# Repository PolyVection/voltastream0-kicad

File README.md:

# VoltaStream ZERO hardware 

PolyVection VoltaStream ZERO is an open source audio streaming solution that runs Linux and features a high quality digital-to-analog converter as well as digital TOSLINK output capability. There is also a 40 way pinheader with access to 28 GPIO's. It is as small as 65 mm x 30 mm and very efficient. This PCB was created using KiCAD 4.0.5.
The whole project is released under the Creative Commons BY-NC-ND 3.0 license. 
For details please refere to the full license text at https://creativecommons.org/licenses/by-nc-nd/3.0/legalcode

If you have any questions don't hesitate to contact us. We are also offering customisation and prototyping services. http://www.voltastream.com

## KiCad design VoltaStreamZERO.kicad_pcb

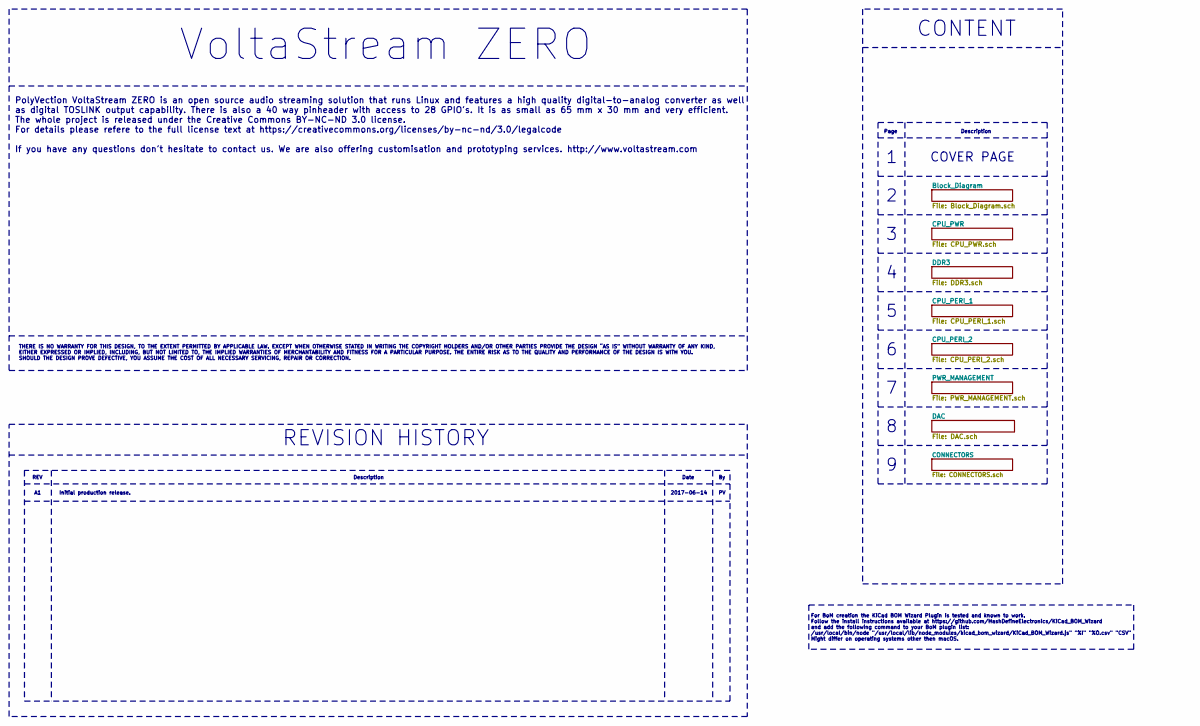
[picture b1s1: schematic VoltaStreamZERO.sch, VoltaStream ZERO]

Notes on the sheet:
VoltaStream ZERO
REVISION HISTORY
CONTENT
THERE IS NO WARRANTY FOR THIS DESIGN, TO THE EXTENT PERMITTED BY APPLICABLE LAW. EXCEPT WHEN OTHERWISE STATED IN WRITING THE COPYRIGHT HOLDERS AND/OR OTHER PARTIES PROVIDE THE DESIGN “AS IS” WITHOUT WARRANTY OF ANY KIND, EITHER EXPRESSED OR IMPLIED, INCLUDING, BUT NOT LIMITED TO, THE IMPLIED WARRAN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
PolyVection VoltaStream ZERO is an open source audio streaming solution that runs Linux and features a high quality digital-to-analog converter as well as digital TOSLINK output capability. There is also a 40 way pinheader with access to 28 GPIO's. It is as small as 65 mm x 30 mm and very efficient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
Page
Description
COVER PAGE
For BoM creation the KiCad BOM Wizard Plugin is tested and known to work. Follow the install instructions available at https://github.com/HashDefineElectronics/KiCad_BOM_Wizard and add the following command to your BoM plugin list: /usr/local/bin/node "/usr/local/lib/node_modules/kicad_bom_wizard/K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
REV
Date
Initial production release.
2017-06-14

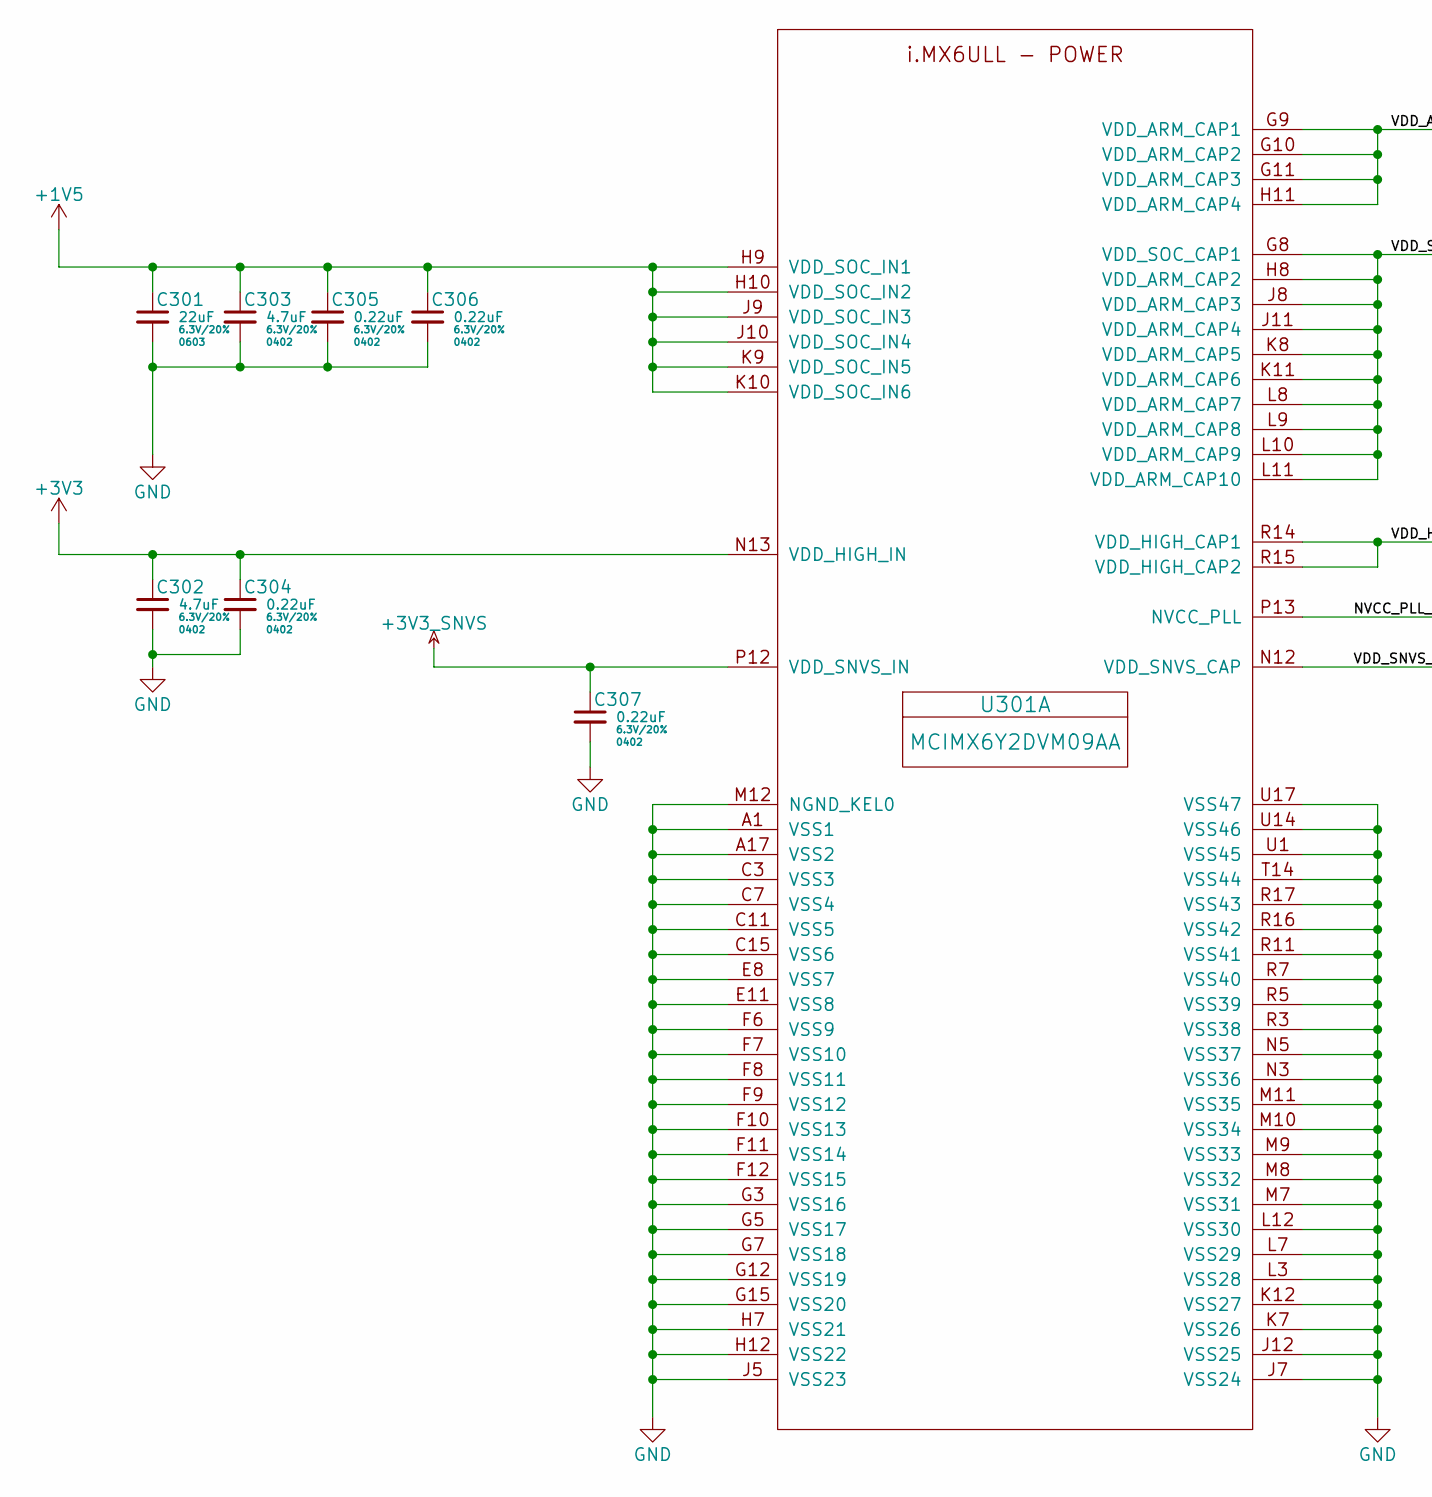
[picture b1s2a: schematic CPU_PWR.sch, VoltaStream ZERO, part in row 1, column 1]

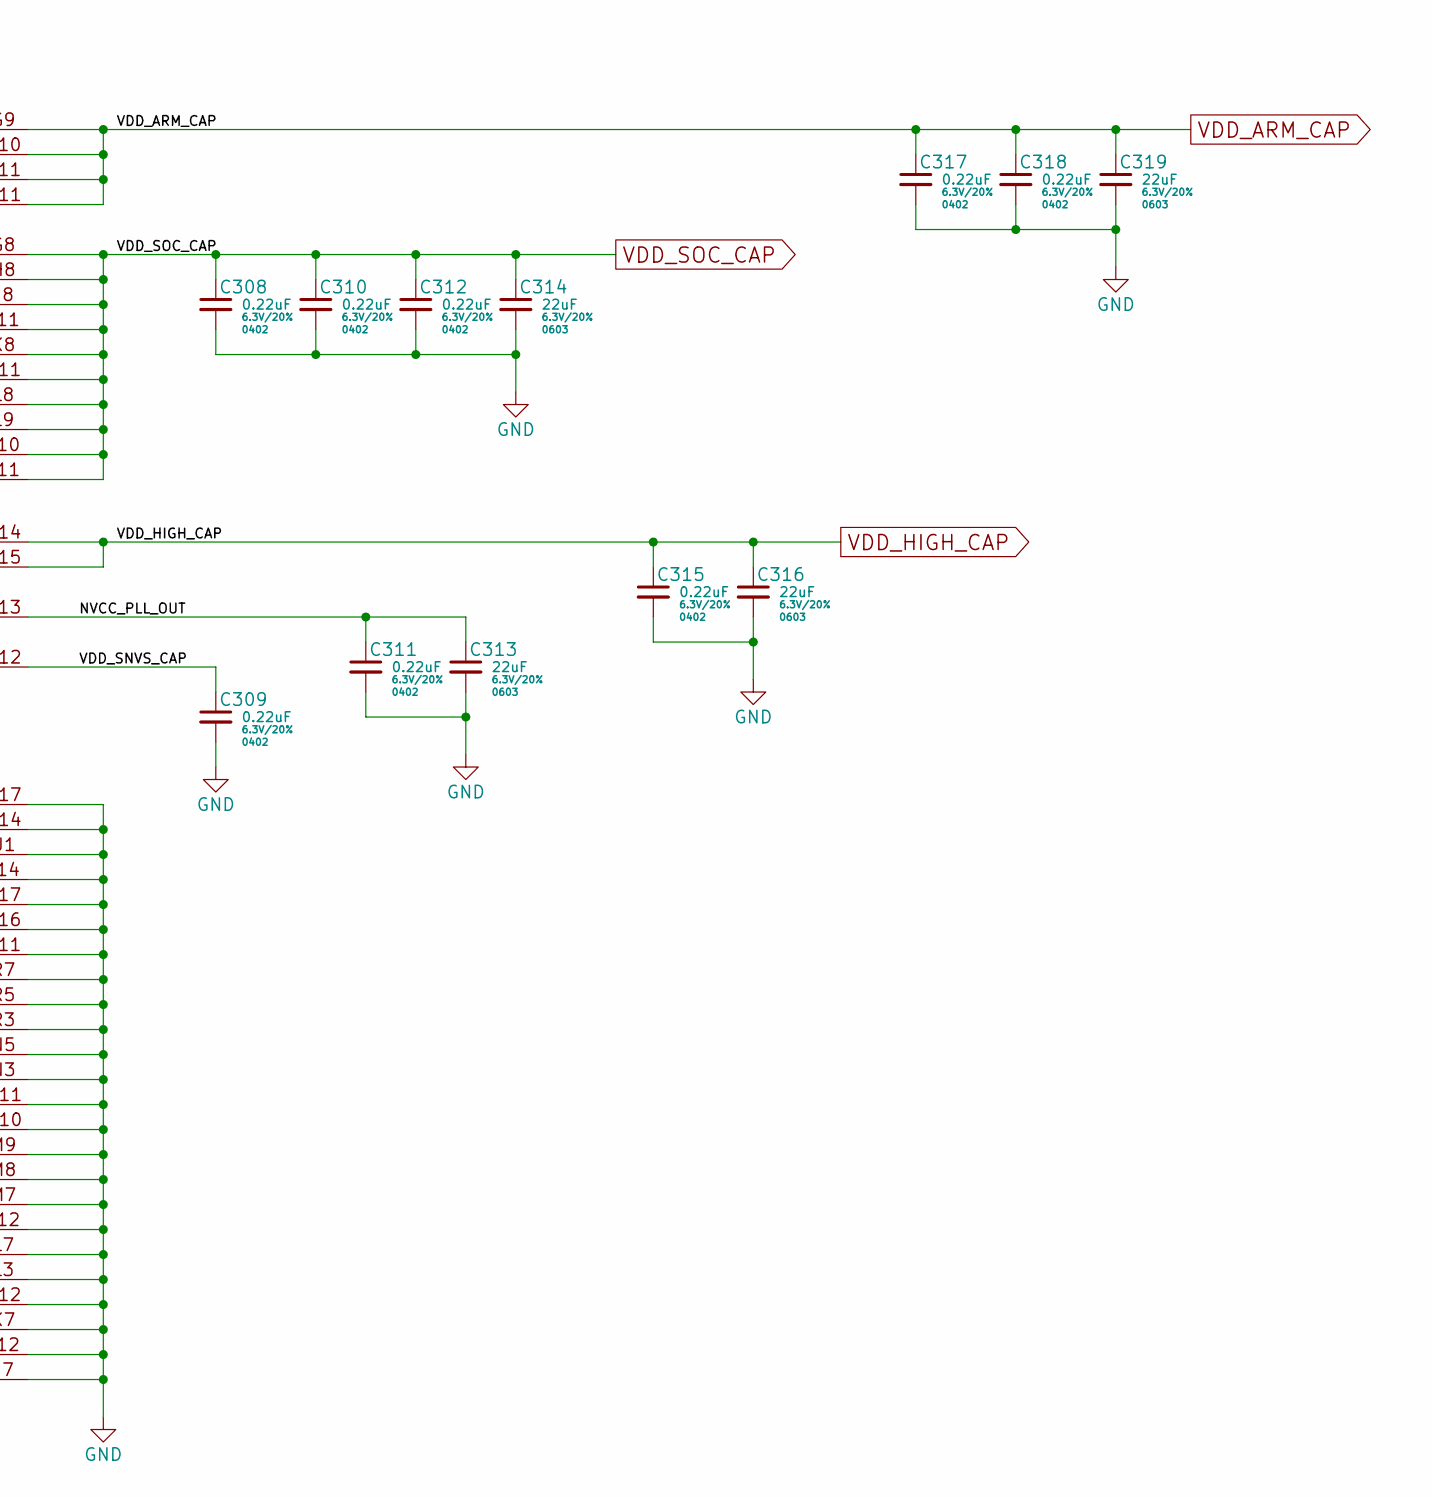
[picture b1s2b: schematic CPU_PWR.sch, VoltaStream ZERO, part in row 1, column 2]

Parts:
C301, C313, C314, C316, C319: 22uF; 0603; Rating 6.3V/20%; Rating2 X5R; Part GRM188R60J226ME0D
C302, C303: 4.7uF; 0402; Rating 6.3V/20%; Rating2 X5R; Part GRM155R60J475ME7D
C304, C305, C306, C307, C308, C309, C310, C311, C312, C315, C317, C318: 0.22uF; 0402; Rating 6.3V/20%; Rating2 X5R; Part GRM155R60J224KE01D
U301: MCIMX6Y2DVM09AA; BGA_14x14; Rating 1x 900 MHz, 32 bit; Part MCIMX6Y2DVM09AA

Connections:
+1V5: C301.1, C303.1, C305.1, C306.1, U301.H9 (VDD_SOC_IN1), U301.H10 (VDD_SOC_IN2), U301.J9 (VDD_SOC_IN3), U301.J10 (VDD_SOC_IN4), U301.K9 (VDD_SOC_IN5), U301.K10 (VDD_SOC_IN6); also elsewhere on the board
+3V3: C302.1, C304.1, U301.N13 (VDD_HIGH_IN); also elsewhere on the board
+3V3_SNVS: C307.1, U301.P12 (VDD_SNVS_IN); also elsewhere on the board
/CPU_PWR/NVCC_PLL_OUT: C311.1, C313.1, U301.P13 (NVCC_PLL)
/CPU_PWR/VDD_SNVS_CAP: C309.1, U301.N12 (VDD_SNVS_CAP)
GND: C301.2, C302.2, C303.2, C304.2, C305.2, C306.2, C307.2, C308.2, C309.2, C310.2, C311.2, C312.2, C313.2, C314.2, C315.2, C316.2, C317.2, C318.2, C319.2, U301.A1 (VSS1), U301.A17 (VSS2), U301.C3 (VSS3), U301.C7 (VSS4), U301.C11 (VSS5), U301.C15 (VSS6), U301.E8 (VSS7), U301.E11 (VSS8), U301.F6 (VSS9), U301.F7 (VSS10), U301.F8 (VSS11), U301.F9 (VSS12), U301.F10 (VSS13), U301.F11 (VSS14), U301.F12 (VSS15), U301.G3 (VSS16), U301.G5 (VSS17), U301.G7 (VSS18), U301.G12 (VSS19), U301.G15 (VSS20), U301.H7 (VSS21), U301.H12 (VSS22), U301.J5 (VSS23), U301.J7 (VSS24), U301.J12 (VSS25), U301.K7 (VSS26), U301.K12 (VSS27), U301.L3 (VSS28), U301.L7 (VSS29), U301.L12 (VSS30), U301.M7 (VSS31), U301.M8 (VSS32), U301.M9 (VSS33), U301.M10 (VSS34), U301.M11 (VSS35), U301.M12 (NGND_KEL0), U301.N3 (VSS36), U301.N5 (VSS37), U301.R3 (VSS38), U301.R5 (VSS39), U301.R7 (VSS40), U301.R11 (VSS41), U301.R16 (VSS42), U301.R17 (VSS43), U301.T14 (VSS44), U301.U1 (VSS45), U301.U14 (VSS46), U301.U17 (VSS47); also elsewhere on the board
VDD_ARM_CAP: C317.1, C318.1, C319.1, U301.G9 (VDD_ARM_CAP1), U301.G10 (VDD_ARM_CAP2), U301.G11 (VDD_ARM_CAP3), U301.H11 (VDD_ARM_CAP4)
VDD_HIGH_CAP: C315.1, C316.1, U301.R14 (VDD_HIGH_CAP1), U301.R15 (VDD_HIGH_CAP2); also elsewhere on the board
VDD_SOC_CAP: C308.1, C310.1, C312.1, C314.1, U301.G8 (VDD_SOC_CAP1), U301.H8 (VDD_ARM_CAP2), U301.J8 (VDD_ARM_CAP3), U301.J11 (VDD_ARM_CAP4), U301.K8 (VDD_ARM_CAP5), U301.K11 (VDD_ARM_CAP6), U301.L8 (VDD_ARM_CAP7), U301.L9 (VDD_ARM_CAP8), U301.L10 (VDD_ARM_CAP9), U301.L11 (VDD_ARM_CAP10)

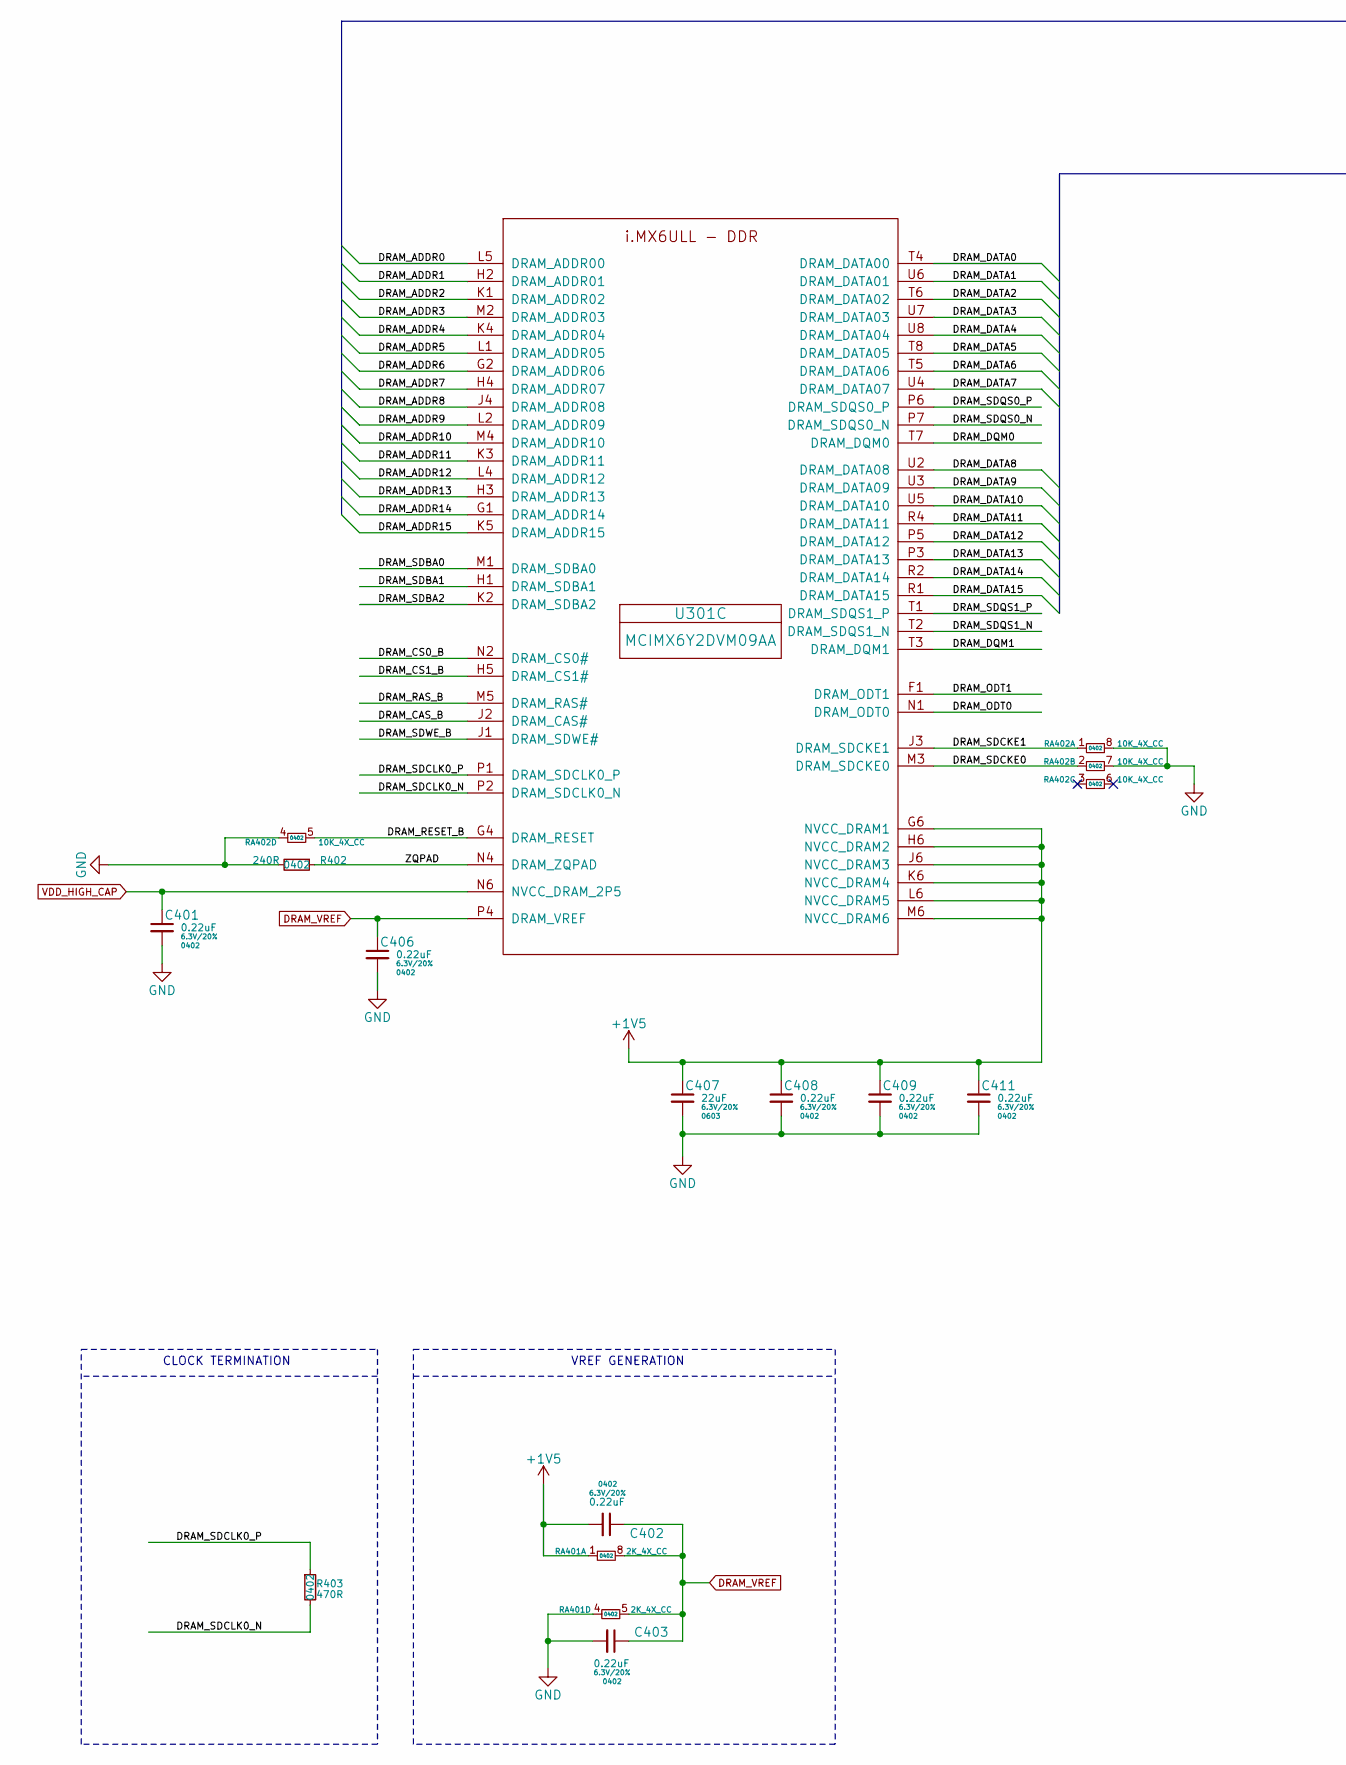
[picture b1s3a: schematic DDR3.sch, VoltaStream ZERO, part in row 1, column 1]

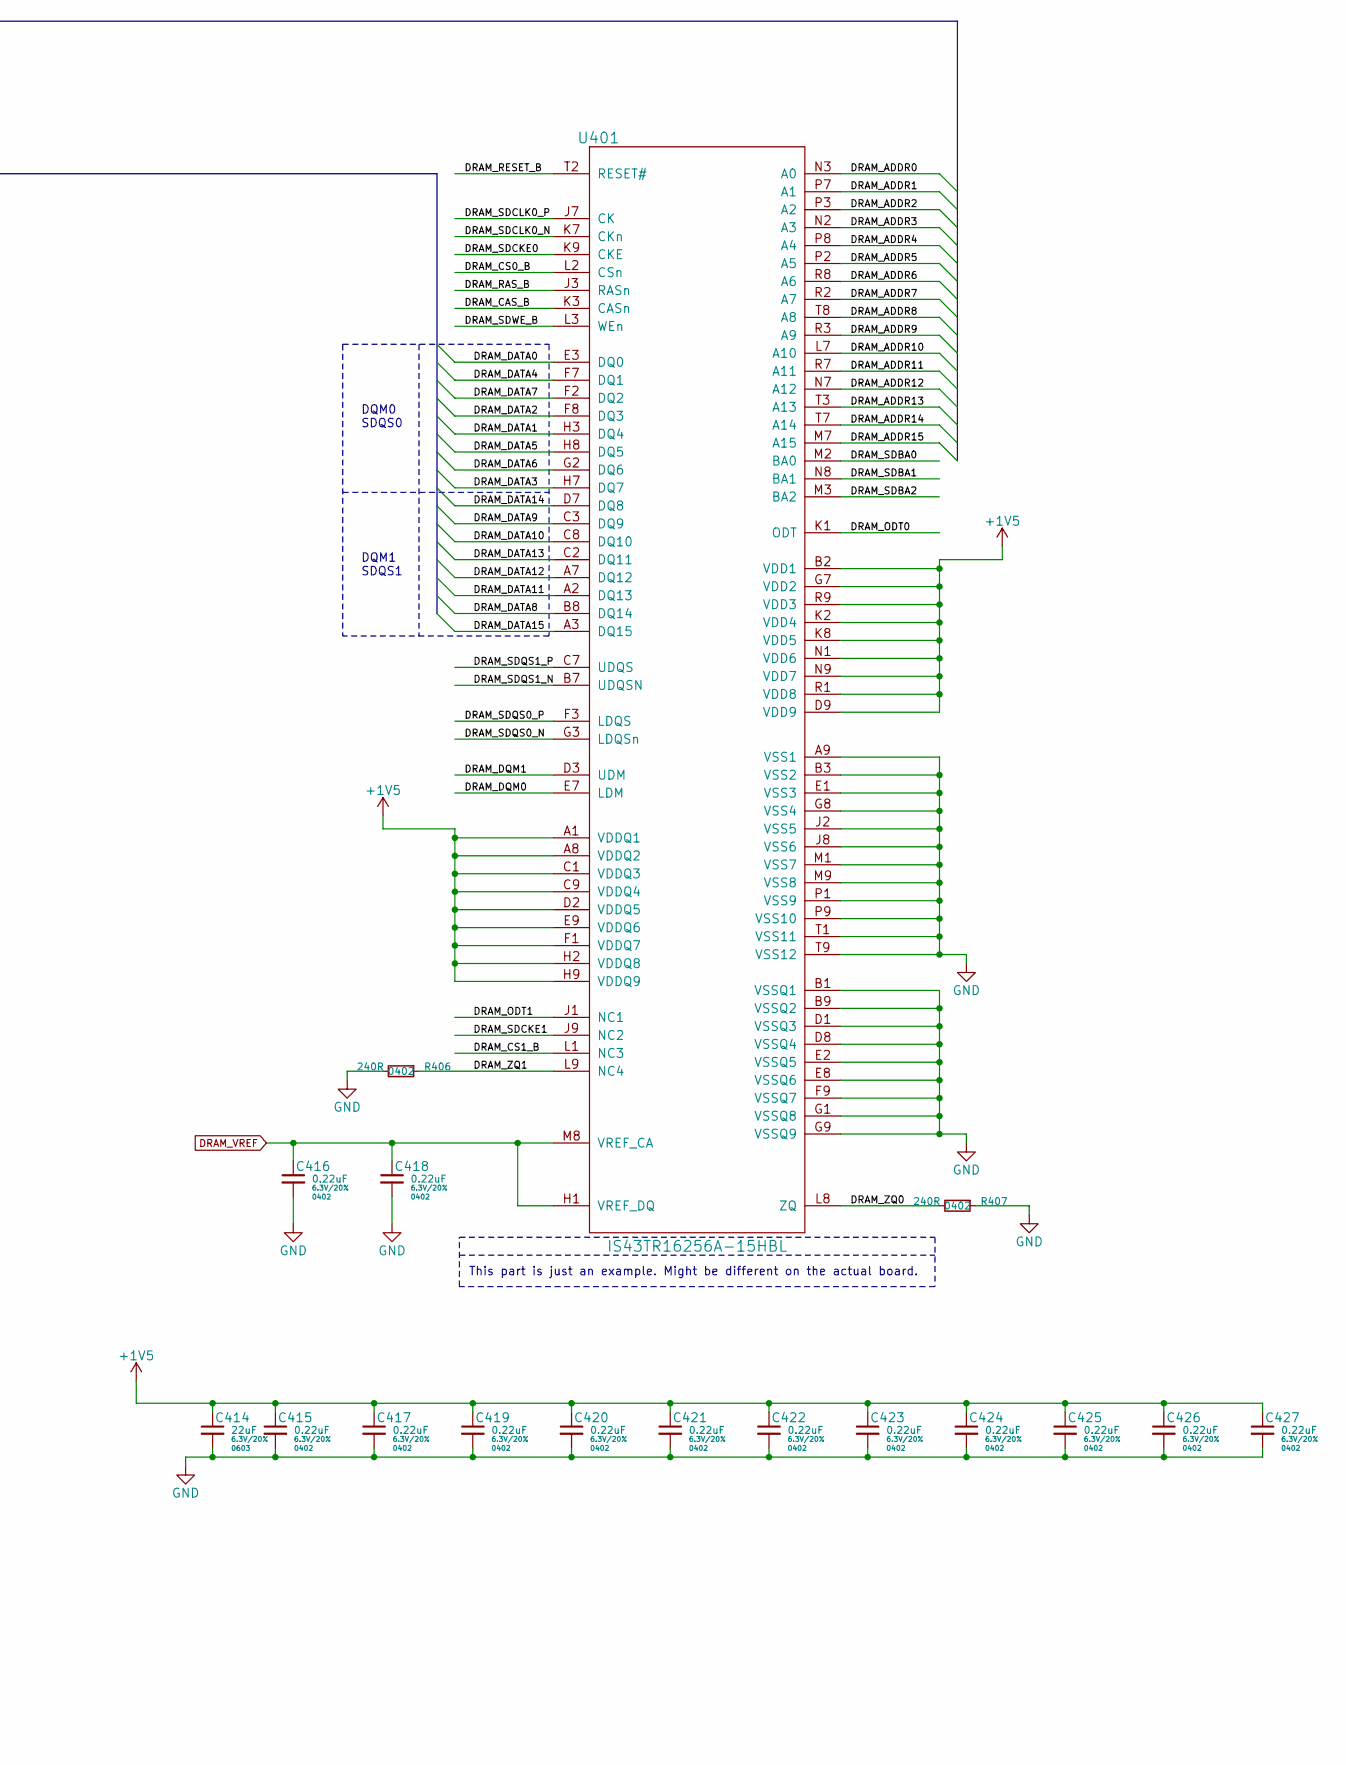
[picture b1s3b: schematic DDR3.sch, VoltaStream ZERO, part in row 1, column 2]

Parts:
C401, C402, C403, C406, C408, C409, C411, C415, C416, C417, C418, C419, C420, C421, C422, C423, C424, C425, C426, C427: 0.22uF; 0402; Rating 6.3V/20%; Rating2 X5R; Part GRM155R60J224KE01D
C407, C414: 22uF; 0603; Rating 6.3V/20%; Rating2 X5R; Part GRM188R60J226ME0D
R402, R406, R407: 240R; 0402; Rating 1% / Thick Film; Part RC0402FR-07240RL
R403: 470R; 0402; Rating 1% / Thick Film; Part RC0402FR-07470RL
RA401: 2K_4X_CC; R_Array_OPT_4x0402; Rating 2K, 5%; Rating2 Concave Array 4x; Part EXB-N8V202JX
RA402: 10K_4X_CC; R_Array_OPT_4x0402; Rating 10K, 5%; Rating2 Concave Array 4x; Part EXB-N8V103JX
U301: MCIMX6Y2DVM09AA; BGA_14x14; Rating 1x 900 MHz, 32 bit; Part MCIMX6Y2DVM09AA
U401: IS43TR16256A-15HBL; FBGA_96_DDR3L; Rating 4G - DDR3; Rating2 512 MB - 1V5; Part IS43TR16256A-15HBL

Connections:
+1V5: C402.2, C407.1, C408.1, C409.1, C411.1, C414.1, C415.1, C417.1, C419.1, C420.1, C421.1, C422.1, C423.1, C424.1, C425.1, C426.1, C427.1, RA401.1, U301.G6 (NVCC_DRAM1), U301.H6 (NVCC_DRAM2), U301.J6 (NVCC_DRAM3), U301.K6 (NVCC_DRAM4), U301.L6 (NVCC_DRAM5), U301.M6 (NVCC_DRAM6), U401.A1 (VDDQ1), U401.A8 (VDDQ2), U401.B2 (VDD1), U401.C1 (VDDQ3), U401.C9 (VDDQ4), U401.D2 (VDDQ5), U401.D9 (VDD9), U401.E9 (VDDQ6), U401.F1 (VDDQ7), U401.G7 (VDD2), U401.H2 (VDDQ8), U401.H9 (VDDQ9), U401.K2 (VDD4), U401.K8 (VDD5), U401.N1 (VDD6), U401.N9 (VDD7), U401.R1 (VDD8), U401.R9 (VDD3); also elsewhere on the board
/DDR3/DRAM_ADDR0: U301.L5 (DRAM_ADDR00), U401.N3 (A0)
/DDR3/DRAM_ADDR1: U301.H2 (DRAM_ADDR01), U401.P7 (A1)
/DDR3/DRAM_ADDR2: U301.K1 (DRAM_ADDR02), U401.P3 (A2)
/DDR3/DRAM_ADDR3: U301.M2 (DRAM_ADDR03), U401.N2 (A3)
/DDR3/DRAM_ADDR4: U301.K4 (DRAM_ADDR04), U401.P8 (A4)
/DDR3/DRAM_ADDR5: U301.L1 (DRAM_ADDR05), U401.P2 (A5)
/DDR3/DRAM_ADDR6: U301.G2 (DRAM_ADDR06), U401.R8 (A6)
/DDR3/DRAM_ADDR7: U301.H4 (DRAM_ADDR07), U401.R2 (A7)
/DDR3/DRAM_ADDR8: U301.J4 (DRAM_ADDR08), U401.T8 (A8)
/DDR3/DRAM_ADDR9: U301.L2 (DRAM_ADDR09), U401.R3 (A9)
/DDR3/DRAM_ADDR10: U301.M4 (DRAM_ADDR10), U401.L7 (A10)
/DDR3/DRAM_ADDR11: U301.K3 (DRAM_ADDR11), U401.R7 (A11)
/DDR3/DRAM_ADDR12: U301.L4 (DRAM_ADDR12), U401.N7 (A12)
/DDR3/DRAM_ADDR13: U301.H3 (DRAM_ADDR13), U401.T3 (A13)
/DDR3/DRAM_ADDR14: U301.G1 (DRAM_ADDR14), U401.T7 (A14)
/DDR3/DRAM_ADDR15: U301.K5 (DRAM_ADDR15), U401.M7 (A15)
/DDR3/DRAM_CAS_B: U301.J2 (DRAM_CAS#), U401.K3 (CASn)
/DDR3/DRAM_CS0_B: U301.N2 (DRAM_CS0#), U401.L2 (CSn)
/DDR3/DRAM_CS1_B: U301.H5 (DRAM_CS1#), U401.L1 (NC3)
/DDR3/DRAM_DATA0: U301.T4 (DRAM_DATA00), U401.E3 (DQ0)
/DDR3/DRAM_DATA1: U301.U6 (DRAM_DATA01), U401.H3 (DQ4)
/DDR3/DRAM_DATA2: U301.T6 (DRAM_DATA02), U401.F8 (DQ3)
/DDR3/DRAM_DATA3: U301.U7 (DRAM_DATA03), U401.H7 (DQ7)
/DDR3/DRAM_DATA4: U301.U8 (DRAM_DATA04), U401.F7 (DQ1)
/DDR3/DRAM_DATA5: U301.T8 (DRAM_DATA05), U401.H8 (DQ5)
/DDR3/DRAM_DATA6: U301.T5 (DRAM_DATA06), U401.G2 (DQ6)
/DDR3/DRAM_DATA7: U301.U4 (DRAM_DATA07), U401.F2 (DQ2)
/DDR3/DRAM_DATA8: U301.U2 (DRAM_DATA08), U401.B8 (DQ14)
/DDR3/DRAM_DATA9: U301.U3 (DRAM_DATA09), U401.C3 (DQ9)
/DDR3/DRAM_DATA10: U301.U5 (DRAM_DATA10), U401.C8 (DQ10)
/DDR3/DRAM_DATA11: U301.R4 (DRAM_DATA11), U401.A2 (DQ13)
/DDR3/DRAM_DATA12: U301.P5 (DRAM_DATA12), U401.A7 (DQ12)
/DDR3/DRAM_DATA13: U301.P3 (DRAM_DATA13), U401.C2 (DQ11)
/DDR3/DRAM_DATA14: U301.R2 (DRAM_DATA14), U401.D7 (DQ8)
/DDR3/DRAM_DATA15: U301.R1 (DRAM_DATA15), U401.A3 (DQ15)
/DDR3/DRAM_DQM0: U301.T7 (DRAM_DQM0), U401.E7 (LDM)
/DDR3/DRAM_DQM1: U301.T3 (DRAM_DQM1), U401.D3 (UDM)
/DDR3/DRAM_ODT0: U301.N1 (DRAM_ODT0), U401.K1 (ODT)
/DDR3/DRAM_ODT1: U301.F1 (DRAM_ODT1), U401.J1 (NC1)
/DDR3/DRAM_RAS_B: U301.M5 (DRAM_RAS#), U401.J3 (RASn)
/DDR3/DRAM_RESET_B: RA402.5 (R1), U301.G4 (DRAM_RESET), U401.T2 (RESET#)
/DDR3/DRAM_SDBA0: U301.M1 (DRAM_SDBA0), U401.M2 (BA0)
/DDR3/DRAM_SDBA1: U301.H1 (DRAM_SDBA1), U401.N8 (BA1)
/DDR3/DRAM_SDBA2: U301.K2 (DRAM_SDBA2), U401.M3 (BA2)
/DDR3/DRAM_SDCKE0: RA402.2 (P1), U301.M3 (DRAM_SDCKE0), U401.K9 (CKE)
/DDR3/DRAM_SDCKE1: RA402.1, U301.J3 (DRAM_SDCKE1), U401.J9 (NC2)
/DDR3/DRAM_SDCLK0_N: R403.2, U301.P2 (DRAM_SDCLK0_N), U401.K7 (CKn)
/DDR3/DRAM_SDCLK0_P: R403.1, U301.P1 (DRAM_SDCLK0_P), U401.J7 (CK)
/DDR3/DRAM_SDQS0_N: U301.P7 (DRAM_SDQS0_N), U401.G3 (LDQSn)
/DDR3/DRAM_SDQS0_P: U301.P6 (DRAM_SDQS0_P), U401.F3 (LDQS)
/DDR3/DRAM_SDQS1_N: U301.T2 (DRAM_SDQS1_N), U401.B7 (UDQSN)
/DDR3/DRAM_SDQS1_P: U301.T1 (DRAM_SDQS1_P), U401.C7 (UDQS)
/DDR3/DRAM_SDWE_B: U301.J1 (DRAM_SDWE#), U401.L3 (WEn)
/DDR3/DRAM_ZQ0: R407.2, U401.L8 (ZQ)
/DDR3/DRAM_ZQ1: R406.1, U401.L9 (NC4)
/DDR3/ZQPAD: R402.1, U301.N4 (DRAM_ZQPAD)
DRAM_VREF: C402.1, C403.1, C406.1, C416.1, C418.1, RA401.5 (R1), RA401.8 (R1), U301.P4 (DRAM_VREF), U401.H1 (VREF_DQ), U401.M8 (VREF_CA)
GND: C401.2, C403.2, C406.2, C407.2, C408.2, C409.2, C411.2, C414.2, C415.2, C416.2, C417.2, C418.2, C419.2, C420.2, C421.2, C422.2, C423.2, C424.2, C425.2, C426.2, C427.2, R402.2, R406.2, R407.1, RA401.4 (P1), RA402.4 (P1), RA402.7 (R1), RA402.8 (R1), U401.A9 (VSS1), U401.B1 (VSSQ1), U401.B3 (VSS2), U401.B9 (VSSQ2), U401.D1 (VSSQ3), U401.D8 (VSSQ4), U401.E1 (VSS3), U401.E2 (VSSQ5), U401.E8 (VSSQ6), U401.F9 (VSSQ7), U401.G1 (VSSQ8), U401.G8 (VSS4), U401.G9 (VSSQ9), U401.J2 (VSS5), U401.J8 (VSS6), U401.M1 (VSS7), U401.M9 (VSS8), U401.P1 (VSS9), U401.P9 (VSS10), U401.T1 (VSS11), U401.T9 (VSS12); also elsewhere on the board
VDD_HIGH_CAP: C401.1, U301.N6 (NVCC_DRAM_2P5); also elsewhere on the board

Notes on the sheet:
CLOCK TERMINATION
VREF GENERATION
This part is just an example. Might be different on the actual board.
DQM0 SDQS0
DQM1 SDQS1

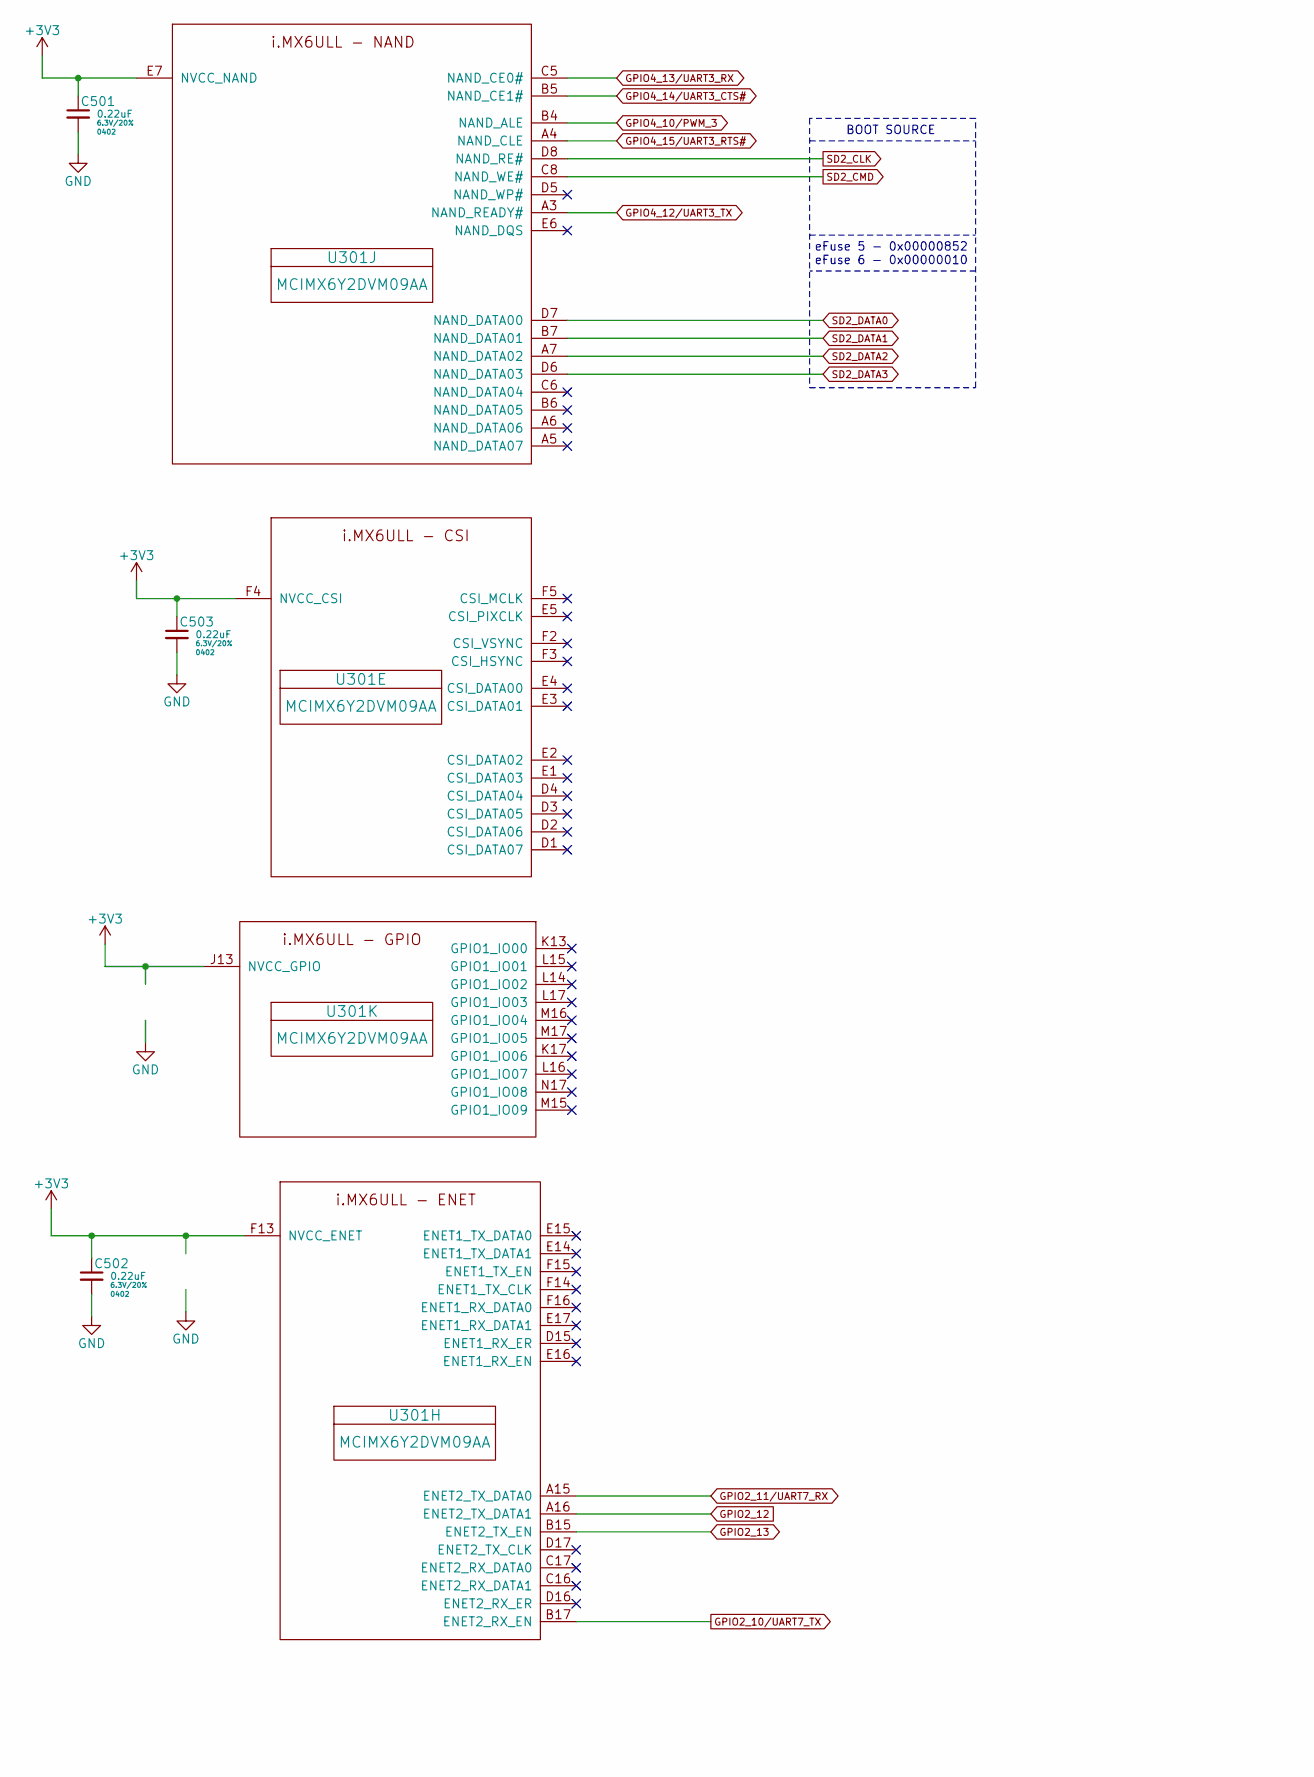
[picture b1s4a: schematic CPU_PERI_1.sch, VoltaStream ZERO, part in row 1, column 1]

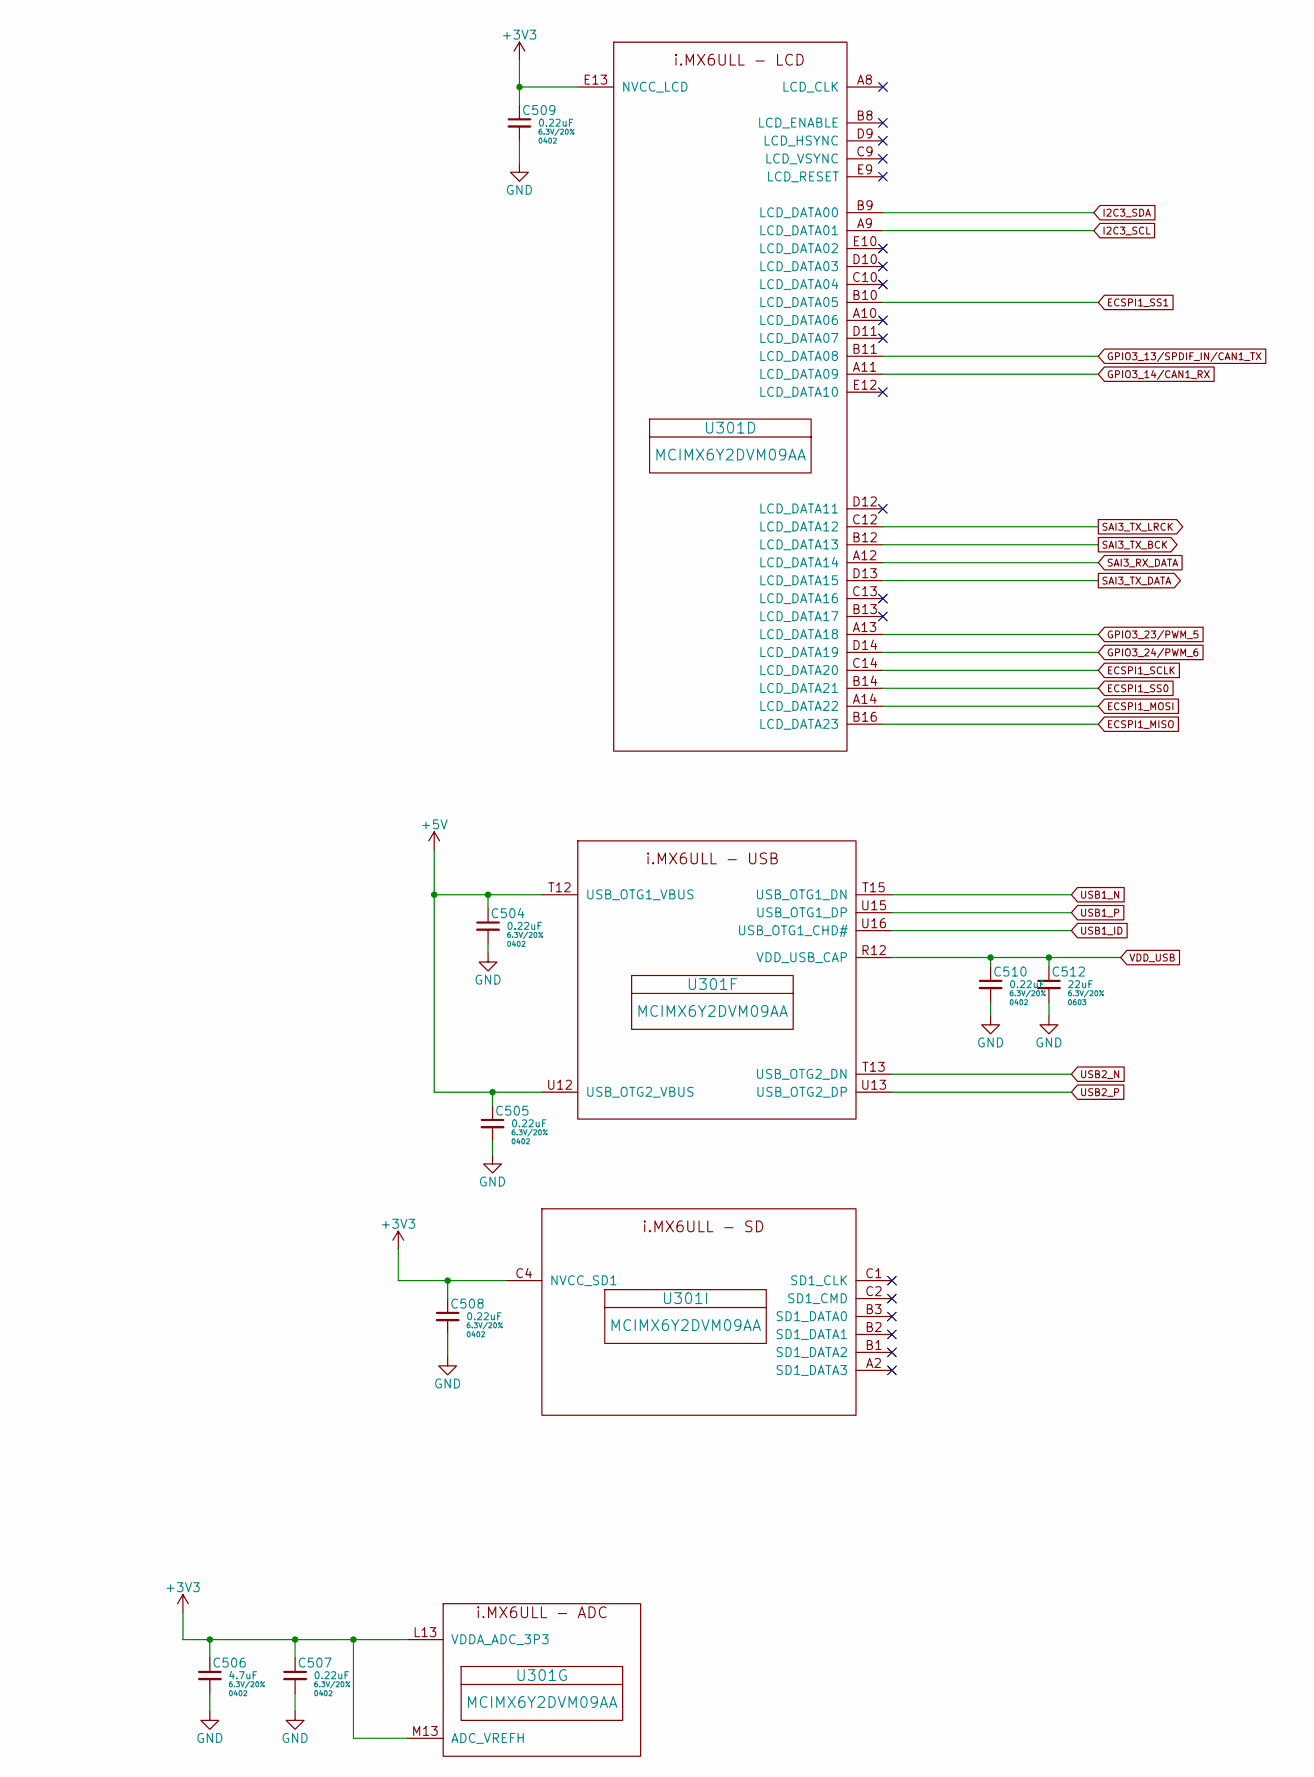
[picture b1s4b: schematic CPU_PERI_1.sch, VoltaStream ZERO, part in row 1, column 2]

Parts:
C501, C502, C503, C504, C505, C507, C508, C509, C510: 0.22uF; 0402; Rating 6.3V/20%; Rating2 X5R; Part GRM155R60J224KE01D
C506: 4.7uF; 0402; Rating 6.3V/20%; Rating2 X5R; Part GRM155R60J475ME7D
C512: 22uF; 0603; Rating 6.3V/20%; Rating2 X5R; Part GRM188R60J226ME0D
U301: MCIMX6Y2DVM09AA; BGA_14x14; Rating 1x 900 MHz, 32 bit; Part MCIMX6Y2DVM09AA

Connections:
+3V3: C501.1, C502.1, C503.1, C506.1, C507.1, C508.1, C509.1, U301.C4 (NVCC_SD1), U301.E7 (NVCC_NAND), U301.E13 (NVCC_LCD), U301.F4 (NVCC_CSI), U301.F13 (NVCC_ENET), U301.J13 (NVCC_GPIO), U301.L13 (VDDA_ADC_3P3), U301.M13 (ADC_VREFH); also elsewhere on the board
+5V: C504.1, C505.1, U301.T12 (USB_OTG1_VBUS), U301.U12 (USB_OTG2_VBUS); also elsewhere on the board
ECSPI1_MISO: U301.B16 (LCD_DATA23); also elsewhere on the board
ECSPI1_MOSI: U301.A14 (LCD_DATA22); also elsewhere on the board
ECSPI1_SCLK: U301.C14 (LCD_DATA20); also elsewhere on the board
ECSPI1_SS0: U301.B14 (LCD_DATA21); also elsewhere on the board
ECSPI1_SS1: U301.B10 (LCD_DATA05); also elsewhere on the board
GND: C501.2, C502.2, C503.2, C504.2, C505.2, C506.2, C507.2, C508.2, C509.2, C510.2, C512.2; also elsewhere on the board
GPIO2_10/UART7_TX: U301.B17 (ENET2_RX_EN); also elsewhere on the board
GPIO2_11/UART7_RX: U301.A15 (ENET2_TX_DATA0); also elsewhere on the board
GPIO2_12: U301.A16 (ENET2_TX_DATA1); also elsewhere on the board
GPIO2_13: U301.B15 (ENET2_TX_EN); also elsewhere on the board
GPIO3_13/SPDIF_IN/CAN1_TX: U301.B11 (LCD_DATA08); also elsewhere on the board
GPIO3_14/CAN1_RX: U301.A11 (LCD_DATA09); also elsewhere on the board
GPIO3_23/PWM_5: U301.A13 (LCD_DATA18); also elsewhere on the board
GPIO3_24/PWM_6: U301.D14 (LCD_DATA19); also elsewhere on the board
GPIO4_10/PWM_3: U301.B4 (NAND_ALE); also elsewhere on the board
GPIO4_12/UART3_TX: U301.A3 (NAND_READY#); also elsewhere on the board
GPIO4_13/UART3_RX: U301.C5 (NAND_CE0#); also elsewhere on the board
GPIO4_14/UART3_CTS#: U301.B5 (NAND_CE1#); also elsewhere on the board
GPIO4_15/UART3_RTS#: U301.A4 (NAND_CLE); also elsewhere on the board
I2C3_SCL: U301.A9 (LCD_DATA01); also elsewhere on the board
I2C3_SDA: U301.B9 (LCD_DATA00); also elsewhere on the board
SAI3_RX_DATA: U301.A12 (LCD_DATA14); also elsewhere on the board
SAI3_TX_BCK: U301.B12 (LCD_DATA13); also elsewhere on the board
SAI3_TX_DATA: U301.D13 (LCD_DATA15); also elsewhere on the board
SAI3_TX_LRCK: U301.C12 (LCD_DATA12); also elsewhere on the board
SD2_CLK: U301.D8 (NAND_RE#); also elsewhere on the board
SD2_CMD: U301.C8 (NAND_WE#); also elsewhere on the board
SD2_DATA0: U301.D7 (NAND_DATA00); also elsewhere on the board
SD2_DATA1: U301.B7 (NAND_DATA01); also elsewhere on the board
SD2_DATA2: U301.A7 (NAND_DATA02); also elsewhere on the board
SD2_DATA3: U301.D6 (NAND_DATA03); also elsewhere on the board
USB1_ID: U301.U16 (USB_OTG1_CHD#)
USB1_N: U301.T15 (USB_OTG1_DN); also elsewhere on the board
USB1_P: U301.U15 (USB_OTG1_DP); also elsewhere on the board
USB2_N: U301.T13 (USB_OTG2_DN); also elsewhere on the board
USB2_P: U301.U13 (USB_OTG2_DP); also elsewhere on the board
VDD_USB: C510.1, C512.1, U301.R12 (VDD_USB_CAP)

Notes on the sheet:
BOOT SOURCE
eFuse 5 - 0x00000852 eFuse 6 - 0x00000010

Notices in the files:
CONNECTORS.sch:
See the full license at https://creativecommons.org/licenses/by-nc-nd/3.0/legalcode
Licensed under Creative Commons BY-NC-ND 3.0
